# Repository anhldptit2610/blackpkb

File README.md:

# blackpkb

A custom macropad made for daily use.

Having a macro pad which we can customize how it works is amazing, especially when working
with CAD softwares. As a electronic hobbyist, I always use KiCAD to draw the PCB for my projects. 
Pressing hotkeys when drawing schematic or PCB is a nuisance if using regular keyboard(in 
my opinion); so I created this project.

## Features

- [x] Customizable function for each key
- [x] Custom profiles(see [this docs](/docs/create-profile.md) for a howto)
- [x] Switch between profiles by pressing built-in rotary encoder button
- [x] adjust volume up/down(You need to map custom key shortcut for volume up/down)

## Requirements

### Hardware
 
 * 1x WeAct's STM32F411CEU6 development board(the BlackPill one)
 * 6x 1N4148 diodes
 * key switches(I desoldered these from a broken keyboard lol)
 * 3x 1kOhm resistor
 * 3x 3mm LEDs, different color(mine is green, red and yellow)
 * a rotary encoder

### Software

 * arm-none-eabi-gcc(my version is 10.3.1)
 * make

You can install above dependencies by using these commands(Ubuntu/any Debian based Linux distro):

    $ sudo apt update
    $ sudo apt install arm-none-eabi-gcc build-essential

## Build steps

    $ git clone https://github.com/anhldptit2610/blackpkb.git
    $ cd blackpkb/firmware/blackpkb
    $ make

You can use the ST's STM32CubeProgrammer to flash the binary.

## TODO

- [x] Use rotary encoder to adjust volume
- [ ] Add LED for each key
- [ ] Make a 3D printed case

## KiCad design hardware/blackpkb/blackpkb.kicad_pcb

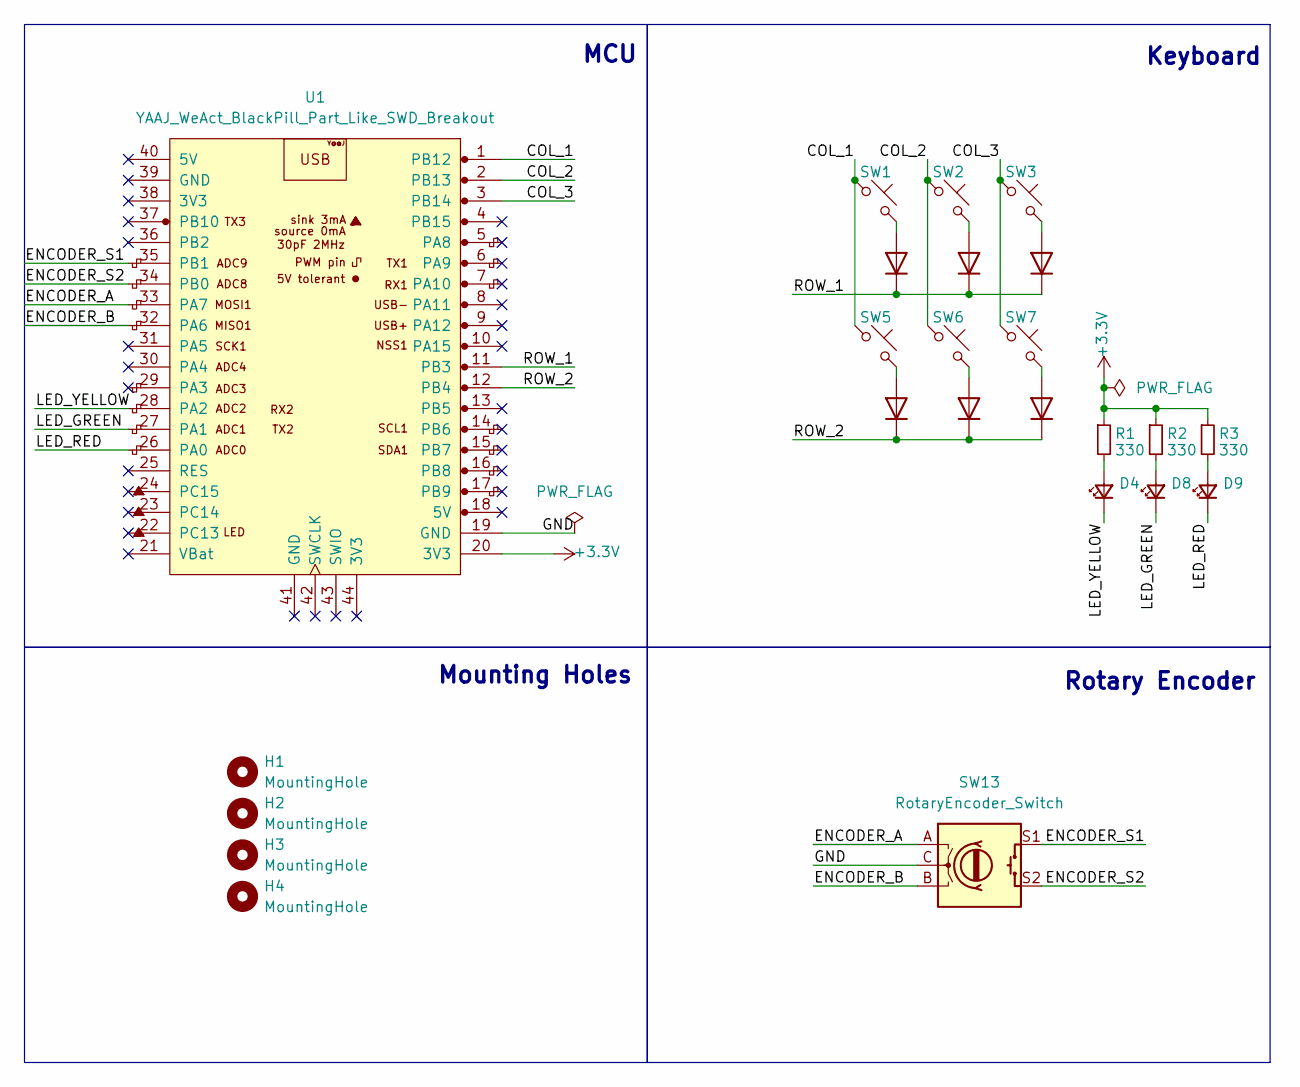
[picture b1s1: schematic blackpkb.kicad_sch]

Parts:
D1, D2, D3, D5, D6, D7: 1N4148; D_DO-35_SOD27_P7.62mm_Horizontal
D4, D8, D9: LED_Small; LED_D3.0mm
H1, H2, H3, H4: MountingHole; MountingHole_2.7mm_M2.5
R1, R2, R3: 330; R_Axial_DIN0207_L6.3mm_D2.5mm_P7.62mm_Horizontal
SW1, SW2, SW3, SW5, SW6, SW7: SW_Push_45deg; SW_Cherry_MX_1.00u_PCB
SW13: RotaryEncoder_Switch; RotaryEncoder_Alps_EC11E-Switch_Vertical_H20mm
U1: YAAJ_WeAct_BlackPill_Part_Like_SWD_Breakout; YAAJ_WeAct_BlackPill_SWD_2

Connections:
+3.3V: R1.1, R2.1, R3.1, U1.20 (3V3)
/COL_1: SW1.1, SW5.1, U1.1 (PB12)
/COL_2: SW2.1, SW6.1, U1.2 (PB13)
/COL_3: SW3.1, SW7.1, U1.3 (PB14)
/ENCODER_A: SW13.A, U1.33 (PA7)
/ENCODER_B: SW13.B, U1.32 (PA6)
/ENCODER_S1: SW13.S1, U1.35 (PB1)
/ENCODER_S2: SW13.S2, U1.34 (PB0)
/GND: SW13.C, U1.19 (GND)
/LED_GREEN: D8.1 (K), U1.27 (PA1)
/LED_RED: D9.1 (K), U1.26 (PA0)
/LED_YELLOW: D4.1 (K), U1.28 (PA2)
/ROW_1: D1.1 (K), D2.1 (K), D3.1 (K), U1.11 (PB3)
/ROW_2: D5.1 (K), D6.1 (K), D7.1 (K), U1.12 (PB4)
unnamed: D1.2 (A), SW1.2
unnamed: D2.2 (A), SW2.2
unnamed: D3.2 (A), SW3.2
unnamed: D4.2 (A), R1.2
unnamed: D5.2 (A), SW5.2
unnamed: D6.2 (A), SW6.2
unnamed: D7.2 (A), SW7.2
unnamed: D8.2 (A), R2.2
unnamed: D9.2 (A), R3.2

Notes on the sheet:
Keyboard
Mounting Holes
MCU
Rotary Encoder

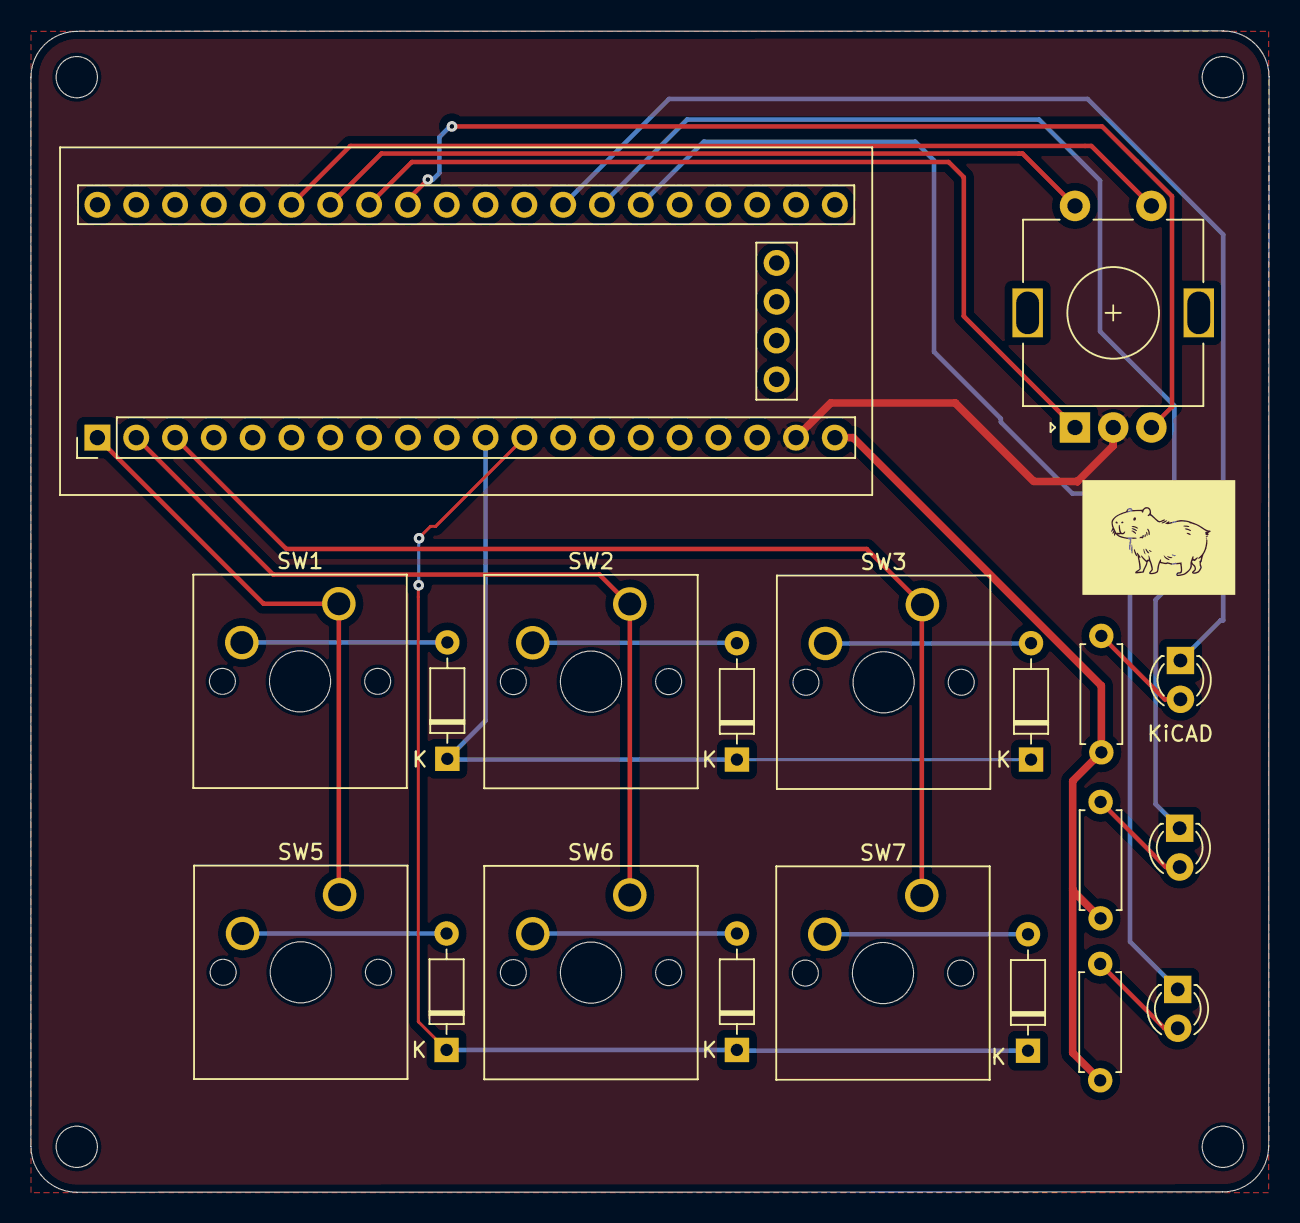
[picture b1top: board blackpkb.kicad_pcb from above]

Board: 2 copper layers, 81.0 x 76.0 mm, 24 parts (0 on the bottom side), 23 nets.

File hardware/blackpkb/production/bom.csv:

Designator,Footprint,Quantity,Value,LCSC Part #
"D1, D2, D3, D5, D6, D7",D_DO-35_SOD27_P7.62mm_Horizontal,6,1N4148,
"D4, D8, D9",LED_D3.0mm,3,LED_Small,
"R1, R2, R3",R_Axial_DIN0207_L6.3mm_D2.5mm_P7.62mm_Horizontal,3,330,
"SW1, SW2, SW3, SW5, SW6, SW7",SW_Cherry_MX_1.00u_PCB,6,SW_Push_45deg,
SW13,RotaryEncoder_Alps_EC11E-Switch_Vertical_H20mm,1,RotaryEncoder_Switch,
U1,YAAJ_WeAct_BlackPill_SWD_2,1,YAAJ_WeAct_BlackPill_Part_Like_SWD_Breakout,

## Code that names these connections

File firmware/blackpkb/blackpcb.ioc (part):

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Mcu.Name=STM32F411C(C-E)Ux
Mcu.Package=UFQFPN48
Mcu.UserName=STM32F411CEUx
PA0-WKUP.GPIOParameters=GPIO_Label
PA0-WKUP.GPIO_Label=LED_YELLOW
PA0-WKUP.Signal=GPIO_Output
PA1.GPIOParameters=GPIO_Label
PA1.GPIO_Label=LED_RED
PA1.Signal=GPIO_Output
PA11.Mode=Device_Only
PA11.Signal=USB_OTG_FS_DM
PA12.Mode=Device_Only
PA12.Signal=USB_OTG_FS_DP
PA2.GPIOParameters=GPIO_Label
PA2.GPIO_Label=LED_GREEN
PA2.Signal=GPIO_Output
PA6.GPIOParameters=GPIO_PuPd,GPIO_Label
PA6.GPIO_Label=ENCODER_B
PA6.GPIO_PuPd=GPIO_PULLUP
PA6.Signal=GPIO_Input
PA7.GPIOParameters=GPIO_PuPd,GPIO_Label
PA7.GPIO_Label=ENCODER_A
PA7.GPIO_PuPd=GPIO_PULLUP
PA7.Signal=GPIO_Input
PB0.GPIOParameters=GPIO_Label
PB0.GPIO_Label=ENCODER_GND
PB0.Signal=GPIO_Output
PB1.GPIOParameters=GPIO_PuPd,GPIO_Label
PB1.GPIO_Label=ENCODER_SW
PB1.GPIO_PuPd=GPIO_PULLUP
PB1.Signal=GPIO_Input
PB12.GPIOParameters=GPIO_Label
PB12.GPIO_Label=COL_1
PB12.Signal=GPIO_Output
PB13.GPIOParameters=GPIO_Label
PB13.GPIO_Label=COL_2
PB13.Signal=GPIO_Output
PB14.GPIOParameters=GPIO_Label
PB14.GPIO_Label=COL_3
PB14.Signal=GPIO_Output
PB3.GPIOParameters=GPIO_PuPd,GPIO_Label
PB3.GPIO_Label=ROW_1
PB3.GPIO_PuPd=GPIO_PULLDOWN
PB3.Signal=GPIO_Input
PB4.GPIOParameters=GPIO_PuPd,GPIO_Label
PB4.GPIO_Label=ROW_2
PB4.GPIO_PuPd=GPIO_PULLDOWN
PB4.Signal=GPIO_Input
PC13-ANTI_TAMP.GPIOParameters=GPIO_Label
PC13-ANTI_TAMP.GPIO_Label=LED
PC13-ANTI_TAMP.Signal=GPIO_Output
PH0\ -\ OSC_IN.Mode=HSE-External-Oscillator
PH0\ -\ OSC_IN.Signal=RCC_OSC_IN
PH1\ -\ OSC_OUT.Mode=HSE-External-Oscillator
PH1\ -\ OSC_OUT.Signal=RCC_OSC_OUT
RCC.HSE_VALUE=8000000
RCC.SYSCLKFreq_VALUE=16000000
board=custom

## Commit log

2024-06-07 first commit. Hardware v0.1 is done
2024-06-07 section the schematic. Add infomations, remove redundant files
2024-07-02 hardware v0.2
2024-07-11 the keyboard now works. Can use one key to type number 1 :>
2024-07-11 remove build folder
2024-07-11 remove compile_commands.json
2024-07-12 Modifier keys work.
2024-07-12 now we can create profiles
2024-07-12 profile now can be selected
2024-07-14 add license and README
2024-07-14 add images of the project
2024-07-14 change image size
2024-07-18 add rotary encoder and mode LEDs. Volume now can be adjusted
2024-07-18 add documents and change some code
2024-07-25 update hardware v2 image
2024-07-25 change some keys in browser profile
